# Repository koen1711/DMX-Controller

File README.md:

# DMX Controller

DMX controller board based on ESP32 NodeMCU. Implementing both plain DMX and RDM while being able to read the entire DMX frame.

## Why?

We have an Theathre stage at school, we do a musical around christmas every year. We wanted to engineer boxes with LED Strips, alarms, etc. 
These things needed to respond with the lighting we already use, so DMX was chosen. Thus I started working on the controllers to control non traditional lights on the stage.

## How?

Now to use the project it's actually pretty simple, you plug in atleast one XLR cable for DMX in the ports, next you wire something up or just use the ESP32 to control DMX.
The possibilities are endless, we engineered it in a way that using a Mesh you can connect more things through one Controller. 

You need the PCB itself, female headers for the ESP32 and the ESP32 itself. Wire up what you need through the GPIO pins.

## Wiring diagram

## Bill of Materials

| Item | Qty. | Price (USD) | Ext. (USD) | Link |
|------|------|-------------|------------|------|
| 470µF 35V Electrolytic Capacitor (C1) | 1 | $0.0576 | $0.06 | [C2836436](https://www.lcsc.com/product-detail/C2836436.html) |
| 100µF 16V Electrolytic Capacitor (C12) | 1 | $0.0101 | $0.01 | [C4747963](https://www.lcsc.com/product-detail/C4747963.html) |
| 180µF 25V Electrolytic Capacitor (C3) | 1 | $0.0240 | $0.02 | [C49233128](https://www.lcsc.com/product-detail/C49233128.html) |
| Schottky Diode 40V 5A SMA (D4) | 1 | $0.0194 | $0.02 | [C22452](https://www.lcsc.com/product-detail/C22452.html) |
| 1x7 Pin Header 2.54mm | 7 | $0.0171 | $0.12 | [C6332200](https://www.lcsc.com/product-detail/C6332200.html) |
| XLR Male Connector - DMX IN (J1) | 1 | $0.3153 | $0.32 | [C309324](https://www.lcsc.com/product-detail/C309324.html) |
| XLR Female Connector - DMX OUT (J2) | 1 | $0.3287 | $0.33 | [C309326](https://www.lcsc.com/product-detail/C309326.html) |
| DC Barrel Jack 2.0mm (J3) | 1 | $0.0296 | $0.03 | [C16214](https://www.lcsc.com/product-detail/C16214.html) |
| 68µH Inductor 0805 (L1) | 1 | $0.0162 | $0.02 | [C275376](https://www.lcsc.com/product-detail/C275376.html) |
| 680Ω 0805 Resistor (R1, R2) | 2 | $0.0017 | $0.00 | [C17798](https://www.lcsc.com/product-detail/C17798.html) |
| 120Ω 0805 Resistor (R3) | 1 | $0.0010 | $0.00 | [C17437](https://www.lcsc.com/product-detail/C17437.html) |
| DPDT Slide Switch (SW1) | 1 | $0.0459 | $0.05 | [C431542](https://www.lcsc.com/product-detail/C431542.html) |
| MAX485 RS-485 Transceiver SO-8 (U1) | 1 | $0.0801 | $0.08 | [C668206](https://www.lcsc.com/product-detail/C668206.html) |
| ESP32 NodeMCU (U3) | 1 | - | - | - |
| XL1509-5.0E1 5V Buck Converter (U4) | 1 | $0.1109 | $0.11 | [C61063](https://www.lcsc.com/product-detail/C61063.html) |
| **Total** | | | **$1.17** | |

*Note: Price excludes U3 (ESP32 NodeMCU) which needs to be sourced separately.*

## Screenshots

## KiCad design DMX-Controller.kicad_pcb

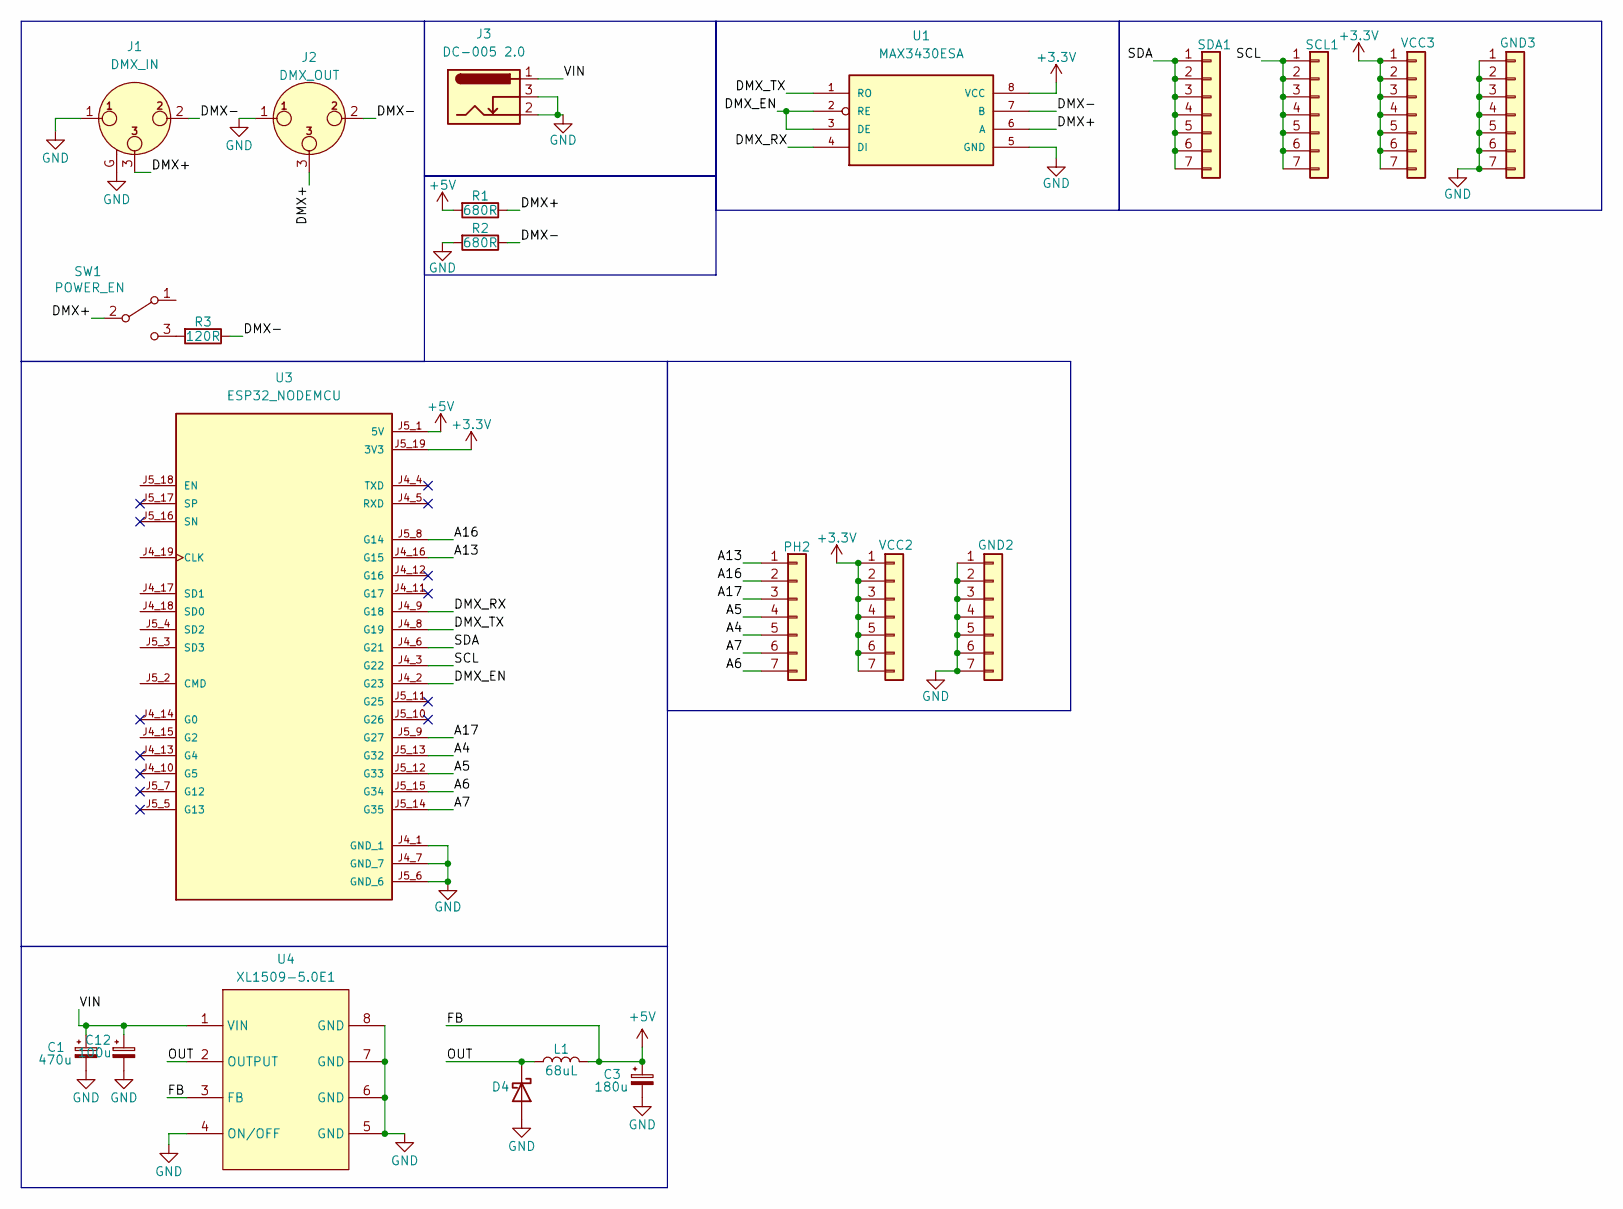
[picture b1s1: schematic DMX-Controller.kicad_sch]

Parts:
C1: 470u; CP_Elec_6.3x7.7; MPN C2836436
C3: 180u; CP_Elec_6.3x7.7; MPN C49233128
C12: 100u; CP_Elec_6.3x7.7; MPN C4747963
D4: D_Schottky; D_SMA; MPN C22452
GND2, GND3: Conn_01x07; PinHeader_1x07_P2.54mm_Vertical; MPN C6332200
J1: DMX_IN; Jack_XLR_Neutrik_NC3MAAH_Horizontal; MPN C309324
J2: DMX_OUT; Jack_XLR_Neutrik_NC3FAAH-0_Horizontal; MPN C309326
J3: DC-005 2.0; BarrelJack_Horizontal; MPN C16214
L1: 68uL; L_0805_2012Metric
PH2: Conn_01x07; PinHeader_1x07_P2.54mm_Vertical; MPN C6332200
R1, R2: 680R; R_0805_2012Metric; MPN C17437
R3: 120R; R_0805_2012Metric; MPN C17437
SCL1: Conn_01x07; PinHeader_1x07_P2.54mm_Vertical; MPN C6332200
SDA1: Conn_01x07; PinHeader_1x07_P2.54mm_Vertical; MPN C6332200
SW1: POWER_EN; SW-TH_MSS22D18GX; MPN C431542
U1: MAX3430ESA; SO08; MPN C668206
U3: ESP32_NODEMCU; MODULE_ESP32_NODEMCU
U4: XL1509-5.0E1; 5V_BUCK; MPN C61063
VCC2, VCC3: Conn_01x07; PinHeader_1x07_P2.54mm_Vertical; MPN C6332200

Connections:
+3.3V: U1.8 (VCC), U3.J5_19 (3V3), VCC2.1, VCC2.2, VCC2.3, VCC2.4, VCC2.5, VCC2.6, VCC2.7, VCC3.1, VCC3.2, VCC3.3, VCC3.4, VCC3.5, VCC3.6, VCC3.7
+5V: C3.1, L1.2, R1.2, U3.J5_1 (5V), U4.3 (FB)
/A4: PH2.5, U3.J5_13 (G32)
/A5: PH2.4, U3.J5_12 (G33)
/A6: PH2.7, U3.J5_15 (G34)
/A7: PH2.6, U3.J5_14 (G35)
/A13: PH2.1, U3.J4_16 (G15)
/A16: PH2.2, U3.J5_8 (G14)
/A17: PH2.3, U3.J5_9 (G27)
/DMX+: J1.3, J2.3, R1.1, SW1.2 (B), U1.6 (A)
/DMX-: J1.2, J2.2, R2.1, R3.1, U1.7 (B)
/DMX_EN: U1.2 (RE), U1.3 (DE), U3.J4_2 (G23)
/DMX_RX: U1.4 (DI), U3.J4_9 (G18)
/DMX_TX: U1.1 (RO), U3.J4_8 (G19)
/OUT: D4.1 (K), L1.1, U4.2 (OUTPUT)
/SCL: SCL1.1, SCL1.2, SCL1.3, SCL1.4, SCL1.5, SCL1.6, SCL1.7, U3.J4_3 (G22)
/SDA: SDA1.1, SDA1.2, SDA1.3, SDA1.4, SDA1.5, SDA1.6, SDA1.7, U3.J4_6 (G21)
/VIN: C1.1, C12.1, J3.1, U4.1 (VIN)
GND: C1.2, C3.2, C12.2, D4.2 (A), GND2.1, GND2.2, GND2.3, GND2.4, GND2.5, GND2.6, GND2.7, GND3.1, GND3.2, GND3.3, GND3.4, GND3.5, GND3.6, GND3.7, J1.1, J1.G, J2.1, J3.2, J3.3, R2.2, U1.5 (GND), U3.J4_1 (GND_1), U3.J4_7 (GND_7), U3.J5_6 (GND_6), U4.4 (ON/OFF), U4.5 (GND), U4.6 (GND), U4.7 (GND), U4.8 (GND)
unnamed: R3.2, SW1.3 (C)

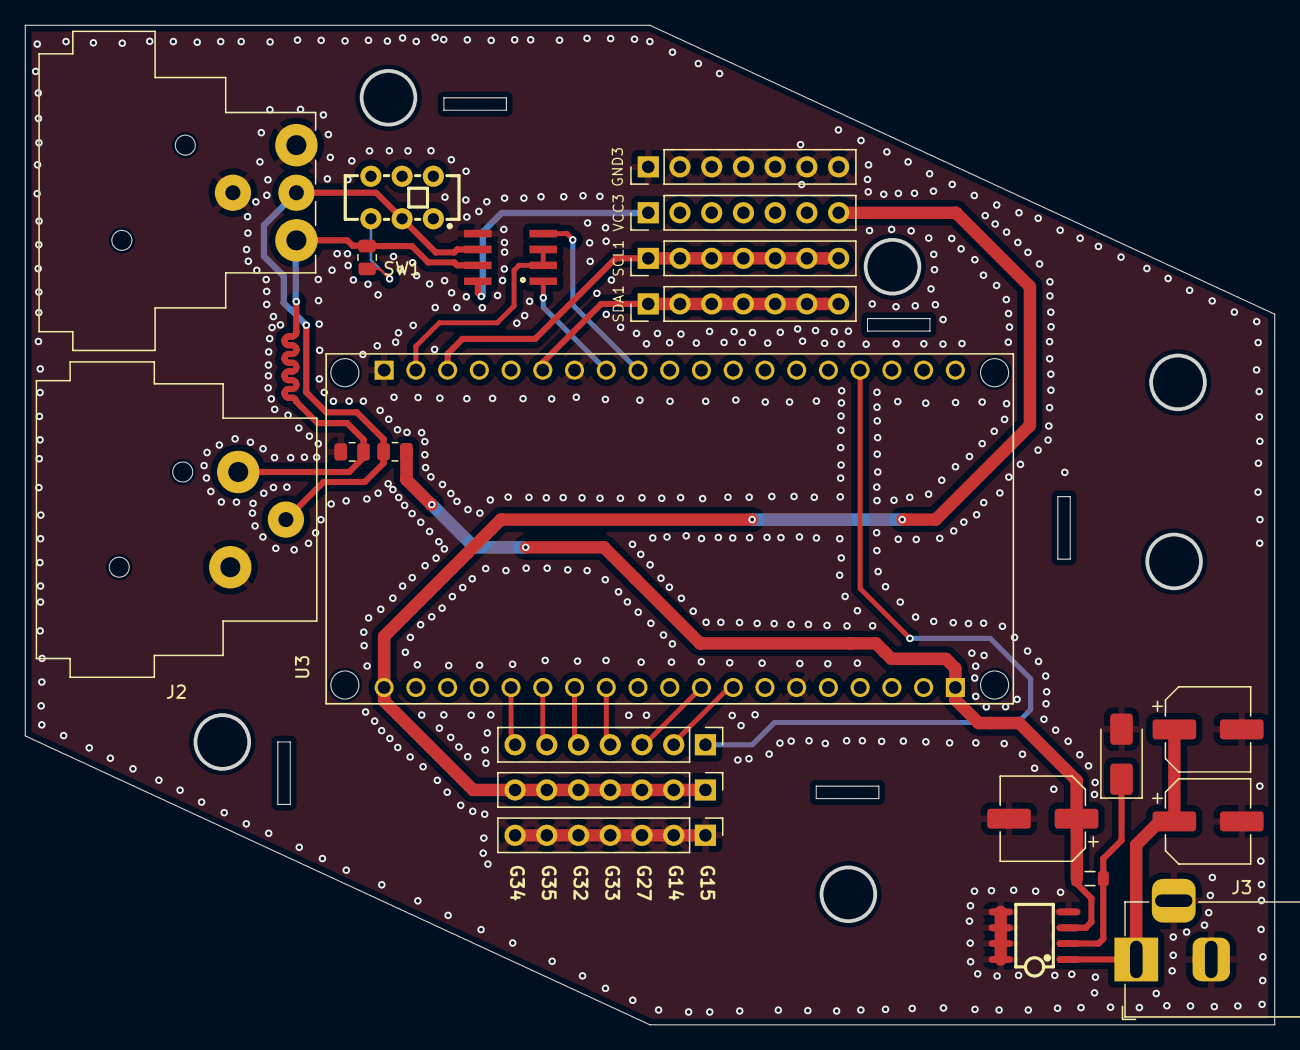
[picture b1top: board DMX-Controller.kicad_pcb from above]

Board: 2 copper layers, 99.8 x 79.8 mm, 22 parts (0 on the bottom side), 20 nets.

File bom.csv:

Designator,Footprint,Quantity,Value,LCSC Part #
C1,CP_Elec_6.3x7.7,1,470u,C2836436
C12,CP_Elec_6.3x7.7,1,100u,C4747963
C3,CP_Elec_6.3x7.7,1,180u,C49233128
D4,D_SMA,1,D_Schottky, C22452
"GND2, GND3, PH2, SCL1, SDA1, VCC2, VCC3",PinHeader_1x07_P2.54mm_Vertical,7,Conn_01x07,C6332200
J1,Jack_XLR_Neutrik_NC3MAAH_Horizontal,1,DMX_IN,C309324
J2,Jack_XLR_Neutrik_NC3FAAH-0_Horizontal,1,DMX_OUT,C309326
J3,BarrelJack_Horizontal,1,DC-005 2.0,C16214
L1,0805,1,68uL,
"R1, R2",0805,2,680R,C17437
R3,0805,1,120R,C17437
SW1,SW-TH_MSS22D18GX,1,POWER_EN,C431542
U1,SO08,1,MAX3430ESA,C668206
U3,MODULE_ESP32_NODEMCU,1,ESP32_NODEMCU,
U4,5V_BUCK,1,XL1509-5.0E1,C61063

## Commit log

2026-01-20 chore: final version of PCB
2026-01-27 chore: add BOM to README.md
2026-01-27 Update README with project details and BOM
    Expanded project description and added context about the DMX controller's purpose for school theatre productions.
2026-01-27 Enhance README with 'Why?' and 'How?' sections
    Added sections explaining the purpose and usage of the DMX controller project.
2026-01-27 chore: fix 3d model
2026-01-27 chore: fix add 3d models
2026-01-27 chore: sort files
2026-01-28 chore: add firmware
2026-02-13 chore: update BOM
